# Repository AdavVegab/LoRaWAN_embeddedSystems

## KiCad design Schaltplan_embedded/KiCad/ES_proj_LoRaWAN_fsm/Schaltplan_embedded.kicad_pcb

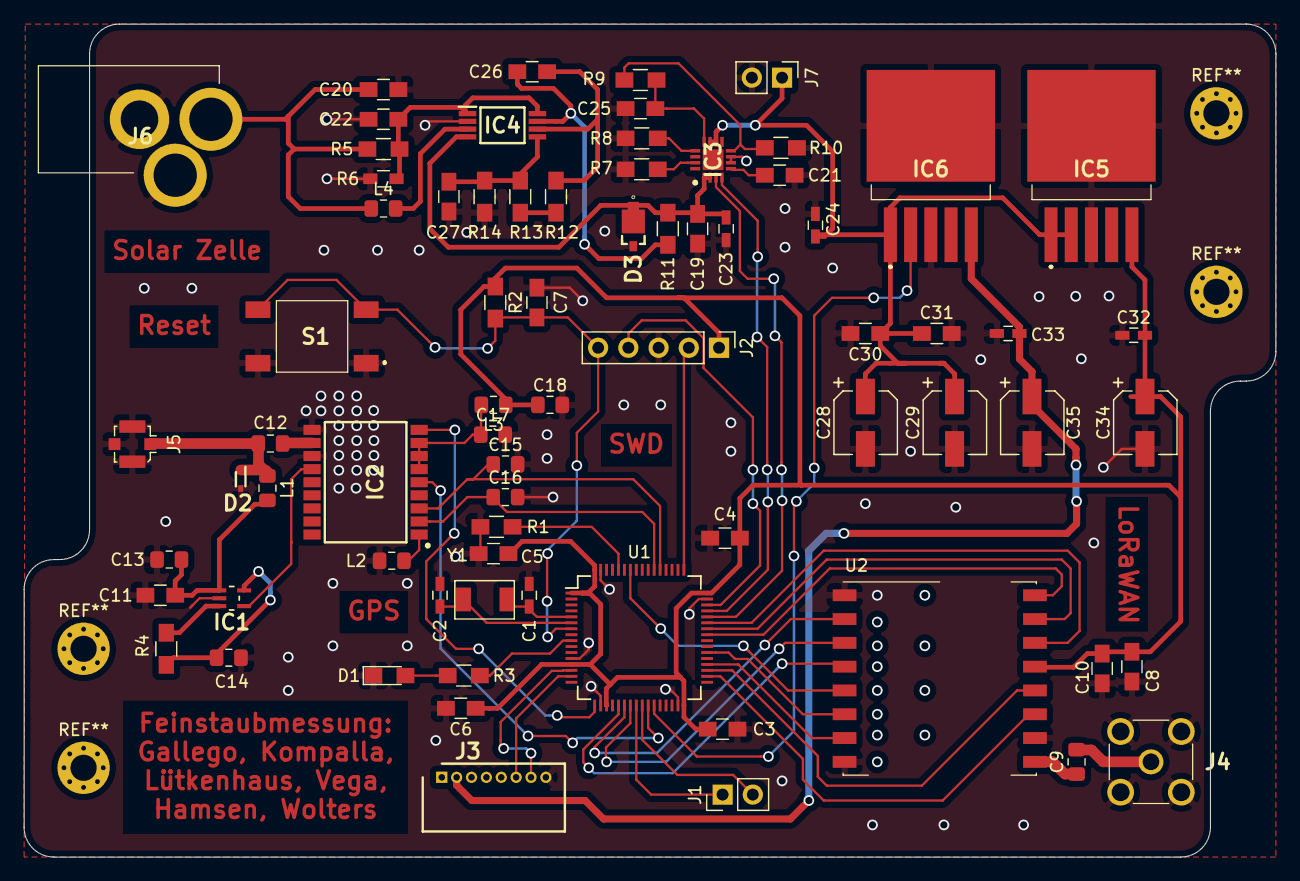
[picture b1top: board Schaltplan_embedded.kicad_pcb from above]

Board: 2 copper layers, 105.2 x 70.0 mm, 73 parts (0 on the bottom side), 57 nets.

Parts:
C1, C2: 20pF; C_0603_HandSoldering
C3, C4, C5, C6, C7, C8, C30, C31: 100nF; C_0805_HandSoldering
C9, C12: 120pF; C_0805_2012Metric_Pad1.15x1.40mm_HandSolder
C10, C19, C26: 1uF; C_0805_HandSoldering
C11: 56pF; C_0805_HandSoldering
C13: 1uF; C_0805_2012Metric_Pad1.15x1.40mm_HandSolder
C14: 2.2uF; C_0805_2012Metric_Pad1.15x1.40mm_HandSolder
C15, C16, C17: 56pF; C_0805_2012Metric_Pad1.15x1.40mm_HandSolder
C18: 10nF; C_0805_2012Metric_Pad1.15x1.40mm_HandSolder
C20: 47uF; C_0805_HandSoldering
C21: 10nF; C_0805_HandSoldering
C22, C25, C27: 1nF; C_0805_HandSoldering
C23: 10uF; C_0603_HandSoldering
C24: 4.7uF; C_0603_HandSoldering
C28, C29: 47uF; CP_Elec_5x5.3
C32, C33: 1uF; C_0603_HandSoldering
C34, C35: 10uF; CP_Elec_5x5.3
D1: LED; LED_0805_HandSoldering
D2: T3V3S5-7; SODFL1608X65N
D3: SMM4F5.0A-TR; STMITE
IC1: TPS22943DCKR; SOT65P210X110-5N
IC2: TESEO-LIV3F; SON110P970X1010X230-18N
IC3: L6924D; QFN50P300X300X100-17N-D
IC4: SPV1040T; SOP65P640X120-8N
IC5: TLS850B0TBV33ATMA1
IC6: TLS850B0TBV55ATMA1; TLS850B0TBV33ATMA1
J1: Conn_01x02; PinHeader_1x02_P2.54mm_Vertical
J2: Conn_01x05; PinHeader_1x05_P2.54mm_Vertical
J3: 53048-0810; SHDR8W35P0X125_1X8_1175X550X370P
J4: CONSMA002-L-G; CONSMA002LG
J5: Conn_Coaxial; U.FL_Molex_MCRF_73412-0110_Vertical
J6: CON-SOCJ-2155; CONSOCJ2155
J7: Conn_01x02; Pin_Header_Straight_1x02_Pitch2.54mm
L1: 56nH; L_0805_2012Metric_Pad1.15x1.40mm_HandSolder
L2: 100nH; L_0805_2012Metric_Pad1.15x1.40mm_HandSolder
L3: 27nH; L_0805_2012Metric_Pad1.15x1.40mm_HandSolder
L4: 10uH; L_0805_2012Metric_Pad1.15x1.40mm_HandSolder
R1, R4: 100k; R_0805_HandSoldering
R2: 4k7; R_0805_HandSoldering
R3: 510; R_0805_HandSoldering
R5, R9, R11, R12: 1k; R_0805_HandSoldering
R6: 3,3m; R_0603_HandSoldering
R7: 24k; R_0805_HandSoldering
R8: 3k3; R_0805_HandSoldering
R10: 470; R_0805_HandSoldering
R13: 2,2M; R_0805_HandSoldering
R14: 820k; R_0805_HandSoldering
S1: LL3301NF065QG
U1: STM32L476RGTx; LQFP-64_10x10mm_Pitch0.5mm
U2: RFM92W_93W; Hopref_RFM9XW_SMD
Y1: ECS-80-12-30Q-DS-TR; Quarz

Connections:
5V_ENABLE: IC6.2, U1.27
+3V3: C3.1, C4.1, C5.1, C6.1, C8.2, C10.2, C18.1, C32.1, C34.1, IC5.5, J2.1, L3.1, R2.1, U1.1, U1.13, U1.19, U1.32, U1.48, U1.64, U2.13
+5V: C33.1, C35.1, IC6.5, J3.2
BAT_STAT1: IC3.3, U1.44
BAT_STAT2: IC3.4, U1.45
GND: C1.1, C2.1, C3.2, C4.2, C5.2, C6.2, C7.2, C8.1, C10.1, C11.2, C13.2, C14.2, C15.2, C16.2, C17.2, C18.2, C19.2, C20.2, C21.2, C22.2, C23.2, C24.2, C25.2, C27.1, C28.2, C29.2, C30.2, C31.2, C32.2, C33.2, C34.2, C35.2, D1.1, D2.2, D3.2, IC1.2, IC2.10, IC2.12, IC3.6, IC3.7, IC4.2, IC5.3, IC5.6, IC6.3, IC6.6, J2.3, J3.8, J4.2, J4.3, J4.4, J4.5, J5.2, J6.2, J6.3, J7.2, L2.2, R1.2, R6.1, R7.1, R8.1, R10.1, R14.2, S1.1, S1.2, U1.12, U1.18, U1.31, U1.47, U1.63, U2.1, U2.8, U2.10
GPS_RSTN: IC2.9, U1.17
GPS_WAKEUP: IC2.5, U1.26
LED_OUT: R3.2, U1.9
LoRa_DI00: U1.43, U2.14
LoRa_DI01: U1.42, U2.15
LoRa_DI02: U1.41, U2.16
LoRa_DI03: U1.34, U2.11
LoRa_DI04: U1.35, U2.12
LoRa_DI05: U1.36, U2.7
LoRa_RESET: U1.38, U2.6
NRST: C7.1, J2.5, R2.2, S1.3, S1.4, U1.7
unnamed: C1.2, U1.5, Y1.1
unnamed: C2.2, U1.6, Y1.2
unnamed: C9.1, U2.9
unnamed: C9.2, J4.1
unnamed: C11.1, C13.1, IC1.1, L1.2
unnamed: C12.1, IC2.11
unnamed: C12.2, D2.1, J5.1, L1.1
unnamed: C14.1, IC1.5, R4.1
unnamed: C17.1, IC2.6, IC2.7, IC2.8, L3.2
unnamed: C20.1, J6.1, L4.1, R5.2
unnamed: C21.1, IC3.5
unnamed: C22.1, IC4.1, IC4.8, R5.1, R6.2
unnamed: C25.1, IC3.12, R9.2
unnamed: C26.1, IC4.7, R11.2
unnamed: C26.2, IC4.6, R12.2
unnamed: C27.2, IC4.5, R13.2, R14.1
unnamed: D1.2, R3.1
unnamed: IC1.3, R4.2
unnamed: IC1.4, IC2.13
unnamed: IC2.1, L2.1
unnamed: IC3.8, R9.1, R10.2
unnamed: IC3.13, R8.2
unnamed: IC3.15, R7.2
unnamed: IC4.3, L4.2
unnamed: R1.1, U1.60
unnamed: R12.1, R13.1
SPI1_MISO: U1.22, U2.2
SPI1_MOSI: U1.23, U2.3
SPI1_NSS: U1.58, U2.5
SPI1_SCK: U1.21, U2.4
SWCLK: J2.2, U1.49
SWDIO: J2.4, U1.46
UART_4_RX: J3.6, U1.15
UART_4_TX: J3.7, U1.14
UART_5_RX: C16.1, IC2.2, U1.54
UART_5_TX: C15.1, IC2.3, U1.53
USART_3_RX: J1.2, U1.25
USART_3_TX: J1.1, U1.24
V_BAT: C24.1, C28.1, C29.1, C30.1, C31.1, IC3.10, IC3.11, IC5.1, IC5.2, IC6.1, J7.1
V_SUPPLY: C19.1, C23.1, D3.1, IC3.1, IC3.2, IC4.4, R11.1

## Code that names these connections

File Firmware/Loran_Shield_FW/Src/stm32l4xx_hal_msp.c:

/* USER CODE BEGIN Header */
/**
  ******************************************************************************
  * File Name          : stm32l4xx_hal_msp.c
  * Description        : This file provides code for the MSP Initialization 
  *                      and de-Initialization codes.
  ******************************************************************************
  * @attention
  *
  * <h2><center>&copy; Copyright (c) 2019 STMicroelectronics.
  * All rights reserved.</center></h2>
  *
  * This software component is licensed by ST under BSD 3-Clause license,
  * the "License"; You may not use this file except in compliance with the
  * License. You may obtain a copy of the License at:
  *                        opensource.org/licenses/BSD-3-Clause
  *
  ******************************************************************************
  */
/* USER CODE END Header */

/* Includes ------------------------------------------------------------------*/
#include "main.h"
/* USER CODE BEGIN Includes */

/* USER CODE END Includes */

/* Private typedef -----------------------------------------------------------*/
/* USER CODE BEGIN TD */

/* USER CODE END TD */

/* Private define ------------------------------------------------------------*/
/* USER CODE BEGIN Define */
 
/* USER CODE END Define */

/* Private macro -------------------------------------------------------------*/
/* USER CODE BEGIN Macro */

/* USER CODE END Macro */

/* Private variables ---------------------------------------------------------*/
/* USER CODE BEGIN PV */

/* USER CODE END PV */

/* Private function prototypes -----------------------------------------------*/
/* USER CODE BEGIN PFP */

/* USER CODE END PFP */

/* External functions --------------------------------------------------------*/
/* USER CODE BEGIN ExternalFunctions */

/* USER CODE END ExternalFunctions */

/* USER CODE BEGIN 0 */

/* USER CODE END 0 */
/**
  * Initializes the Global MSP.
  */
void HAL_MspInit(void)
{
  /* USER CODE BEGIN MspInit 0 */

  /* USER CODE END MspInit 0 */

  __HAL_RCC_SYSCFG_CLK_ENABLE();
  __HAL_RCC_PWR_CLK_ENABLE();

  /* System interrupt init*/

  /* USER CODE BEGIN MspInit 1 */

  /* USER CODE END MspInit 1 */
}

/**
* @brief SPI MSP Initialization
* This function configures the hardware resources used in this example
* @param hspi: SPI handle pointer
* @retval None
*/
void HAL_SPI_MspInit(SPI_HandleTypeDef* hspi)
{
  GPIO_InitTypeDef GPIO_InitStruct = {0};
  if(hspi->Instance==SPI1)
  {
  /* USER CODE BEGIN SPI1_MspInit 0 */

  /* USER CODE END SPI1_MspInit 0 */
    /* Peripheral clock enable */
    __HAL_RCC_SPI1_CLK_ENABLE();
  
    __HAL_RCC_GPIOA_CLK_ENABLE();
    /**SPI1 GPIO Configuration    
    PA5     ------> SPI1_SCK
    PA6     ------> SPI1_MISO
    PA7     ------> SPI1_MOSI 
    */
    GPIO_InitStruct.Pin = GPIO_PIN_5|GPIO_PIN_6|GPIO_PIN_7;
    GPIO_InitStruct.Mode = GPIO_MODE_AF_PP;
    GPIO_InitStruct.Pull = GPIO_NOPULL;
    GPIO_InitStruct.Speed = GPIO_SPEED_FREQ_VERY_HIGH;
    GPIO_InitStruct.Alternate = GPIO_AF5_SPI1;
    HAL_GPIO_Init(GPIOA, &GPIO_InitStruct);

  /* USER CODE BEGIN SPI1_MspInit 1 */

  /* USER CODE END SPI1_MspInit 1 */
  }

}

/**
* @brief SPI MSP De-Initialization
* This function freeze the hardware resources used in this example
* @param hspi: SPI handle pointer
* @retval None
*/
void HAL_SPI_MspDeInit(SPI_HandleTypeDef* hspi)
{
  if(hspi->Instance==SPI1)
  {
  /* USER CODE BEGIN SPI1_MspDeInit 0 */

  /* USER CODE END SPI1_MspDeInit 0 */
    /* Peripheral clock disable */
    __HAL_RCC_SPI1_CLK_DISABLE();
  
    /**SPI1 GPIO Configuration    
    PA5     ------> SPI1_SCK
    PA6     ------> SPI1_MISO
    PA7     ------> SPI1_MOSI 
    */
    HAL_GPIO_DeInit(GPIOA, GPIO_PIN_5|GPIO_PIN_6|GPIO_PIN_7);

  /* USER CODE BEGIN SPI1_MspDeInit 1 */

  /* USER CODE END SPI1_MspDeInit 1 */
  }

}

/**
* @brief TIM_OC MSP Initialization
* This function configures the hardware resources used in this example
* @param htim_oc: TIM_OC handle pointer
* @retval None
*/
void HAL_TIM_OC_MspInit(TIM_HandleTypeDef* htim_oc)
{
  if(htim_oc->Instance==TIM4)
  {
  /* USER CODE BEGIN TIM4_MspInit 0 */

  /* USER CODE END TIM4_MspInit 0 */
    /* Peripheral clock enable */
    __HAL_RCC_TIM4_CLK_ENABLE();
    /* TIM4 interrupt Init */
    HAL_NVIC_SetPriority(TIM4_IRQn, 0, 0);
    HAL_NVIC_EnableIRQ(TIM4_IRQn);
  /* USER CODE BEGIN TIM4_MspInit 1 */

  /* USER CODE END TIM4_MspInit 1 */
  }

}

/**
* @brief TIM_OC MSP De-Initialization
* This function freeze the hardware resources used in this example
* @param htim_oc: TIM_OC handle pointer
* @retval None
*/
void HAL_TIM_OC_MspDeInit(TIM_HandleTypeDef* htim_oc)
{
  if(htim_oc->Instance==TIM4)
  {
  /* USER CODE BEGIN TIM4_MspDeInit 0 */

  /* USER CODE END TIM4_MspDeInit 0 */
    /* Peripheral clock disable */
    __HAL_RCC_TIM4_CLK_DISABLE();

    /* TIM4 interrupt DeInit */
    HAL_NVIC_DisableIRQ(TIM4_IRQn);
  /* USER CODE BEGIN TIM4_MspDeInit 1 */

  /* USER CODE END TIM4_MspDeInit 1 */
  }

}

/**
* @brief UART MSP Initialization
* This function configures the hardware resources used in this example
* @param huart: UART handle pointer
* @retval None
*/
void HAL_UART_MspInit(UART_HandleTypeDef* huart)
{
  GPIO_InitTypeDef GPIO_InitStruct = {0};
  if(huart->Instance==USART2)
  {
  /* USER CODE BEGIN USART2_MspInit 0 */

  /* USER CODE END USART2_MspInit 0 */
    /* Peripheral clock enable */
    __HAL_RCC_USART2_CLK_ENABLE();
  
    __HAL_RCC_GPIOA_CLK_ENABLE();
    /**USART2 GPIO Configuration    
    PA2     ------> USART2_TX
    PA3     ------> USART2_RX 
    */
    GPIO_InitStruct.Pin = GPIO_PIN_2|GPIO_PIN_3;
    GPIO_InitStruct.Mode = GPIO_MODE_AF_PP;
    GPIO_InitStruct.Pull = GPIO_NOPULL;
    GPIO_InitStruct.Speed = GPIO_SPEED_FREQ_VERY_HIGH;
    GPIO_InitStruct.Alternate = GPIO_AF7_USART2;
    HAL_GPIO_Init(GPIOA, &GPIO_InitStruct);

  /* USER CODE BEGIN USART2_MspInit 1 */

  /* USER CODE END USART2_MspInit 1 */
  }

}

/**
* @brief UART MSP De-Initialization
* This function freeze the hardware resources used in this example
* @param huart: UART handle pointer
* @retval None
*/
void HAL_UART_MspDeInit(UART_HandleTypeDef* huart)
{
  if(huart->Instance==USART2)
  {
  /* USER CODE BEGIN USART2_MspDeInit 0 */

  /* USER CODE END USART2_MspDeInit 0 */
    /* Peripheral clock disable */
    __HAL_RCC_USART2_CLK_DISABLE();
  
    /**USART2 GPIO Configuration    
    PA2     ------> USART2_TX
    PA3     ------> USART2_RX 
    */
    HAL_GPIO_DeInit(GPIOA, GPIO_PIN_2|GPIO_PIN_3);

  /* USER CODE BEGIN USART2_MspDeInit 1 */

  /* USER CODE END USART2_MspDeInit 1 */
  }

}

/* USER CODE BEGIN 1 */

/* USER CODE END 1 */

/************************ (C) COPYRIGHT STMicroelectronics *****END OF FILE****/

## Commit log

2019-10-29 add ignore
2019-10-30 test commit
2019-10-30 test excel
2019-10-30 Stückliste von den wichtigsten Teilen
2019-10-30 überflüssige testdateien entfernt
2019-11-05 schaltplan erstellt
2019-11-05 test
2019-11-05 bibliotheken
2019-11-06 Datenblatt für den Battery Charger
2019-11-06 hier das richtige datenblatt
2019-11-06 weitere Datenblätter
2019-11-06 Schaltplan Update und neue Bibliothek
2019-11-07 Neuer Schaltplan und Bibiliotheken
2019-11-13 Datenb
2019-11-13 datenblatt für gps filter
2019-11-13 Revert "datenblatt für gps filter"
    This reverts commit a3d22b48922b2eb581d59a813ce0770eb9a4f51b.
2019-11-13 datenblätter rf
2019-11-13 Datenblätter Update
2019-11-13 alle datenblätter umbenannt. doppelte entfernt
2019-11-13 Neue Stückliste
2019-11-13 schaltplan neu
2019-11-13 Antenna_GPS_Patch_Nicht/4_MuyBuena_Importante
2019-11-13 fixe_problema_muy_importante_fatal_error_proyecta
2019-11-13 anadido_manualmente
2019-11-18 Schaltung_Keramik_Antenne
2019-11-18 Stuckliste/Dattenblatt_PatchAntenna
2019-11-20 stückliste
2019-11-21 Add new directory for the Firmware
2019-11-21 Firs working Version of the Firmware (Nucleo Board)
2019-11-21 Neuer Schaltplan
2019-11-23 Bauteilliste vollständig und Schaltplan entsprechend geändert
2019-11-26 no message
2019-11-26 Pin_änderung_KeinPush
2019-11-26 Firmware stable with new Pin asociations
2019-11-28 Schaltplanänderung
2019-11-28 Neue Bibliothek
2019-11-28 Fail
2019-11-28 ignore
2019-11-28 knhkj
2019-11-28 stabile version
2019-11-28 pfad angepasst
2019-11-28 fix name
2019-11-28 Schaltplan nuevo
2019-12-03 layout
2019-12-03 pcb erweitert
2019-12-04 schaltplan
2019-12-04 Ruteado semi listo
2019-12-05 Firmware for the testing of the Sensors
2019-12-10 präsentation für den vortrag heute
2019-12-10 Schaltplan vervollständigt mit Massefläche
2019-12-10 push
2019-12-10 Schaltplan vervollständigtinkl. Massefläche
2019-12-10 Präsentation erweitert
2019-12-10 Added the Firmware to the präsi
2019-12-10 Cambio tierra
2019-12-10 add images to ppt
2019-12-10 Präsi
2019-12-11 Neue platine
2019-12-11 git :)
2019-12-11 git fix attempt no. 10231931231410294124
2019-12-12 PCB decorations / Gerber Files
2019-12-12 Antenna conn change / layout fixes
2019-12-12 Gerber files
2019-12-12 Stecker gedreht
2019-12-12 Berger files
2020-01-22 New library for the Honeywell sensor
2020-01-27 Working Read and Send Data from LQS
2020-01-27 Cleaning of the Code
2020-01-29 Upload .project
2020-01-30 Bug correction in Bitrate of Air sensor
2020-02-01 Gehäuse
2020-03-13 User configuration corrections, and solved Warnings
2020-06-16 Last Commit (DEPRECATED)
